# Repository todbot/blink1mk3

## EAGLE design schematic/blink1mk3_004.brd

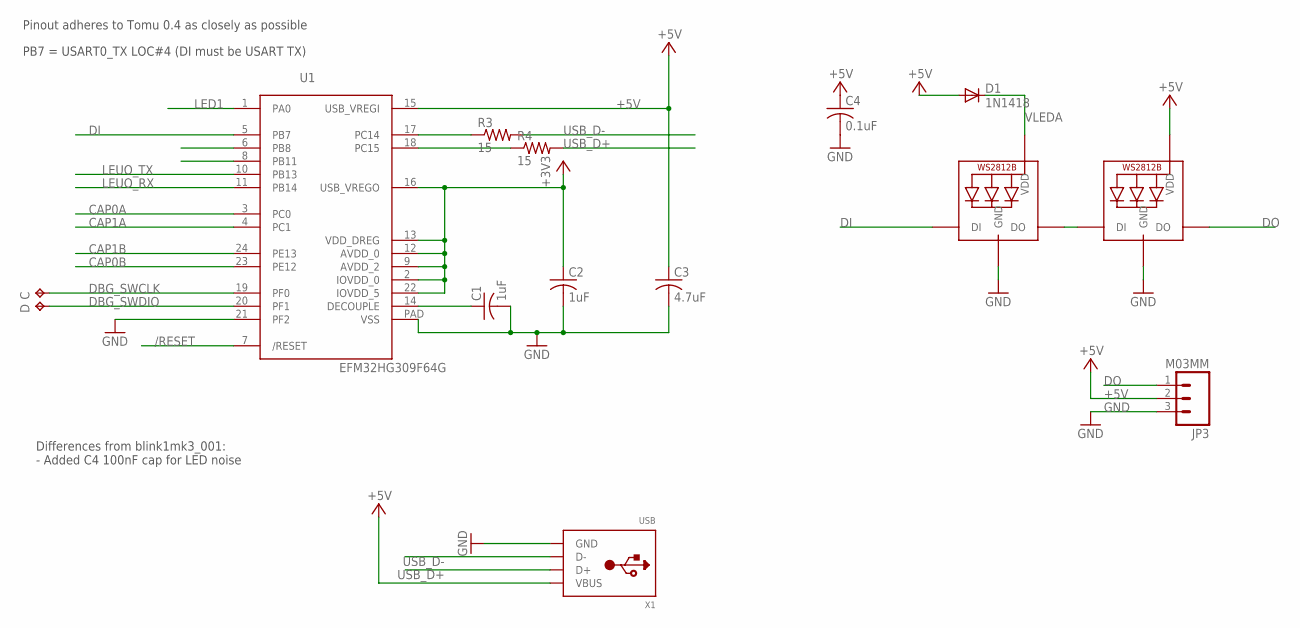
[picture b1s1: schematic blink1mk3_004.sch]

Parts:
C: TPTP10R; TP10R
C1, C2: 1uF; C0402
C3: 4.7uF; C0402
C4: 0.1uF; C0402
D: TPTP10R; TP10R
D1: 1N1418; SOD523
JP3: M03MM; 1X03-1.5MM
LED1, LED2: WS2812B3535; LED3535
R3, R4: 15; R0402
U1: EFM32HG309F64G; QFN24PAD
X1: USB; MOLEX-48037-1000

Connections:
+3V3: C2.1, U1.2 (IOVDD_0), U1.9 (AVDD_2), U1.12 (AVDD_0), U1.13 (VDD_DREG), U1.16 (USB_VREGO), U1.22 (IOVDD_5)
+5V: C3.1, C4.1, D1.A, JP3.2, LED2.2 (VDD), U1.15 (USB_VREGI), X1.1 (VBUS)
/RESET: U1.7 (/RESET)
CAP0A: U1.3 (PC0)
CAP0B: U1.23 (PE12)
CAP1A: U1.4 (PC1)
CAP1B: U1.24 (PE13)
DBG_SWCLK: C.TP, U1.19 (PF0)
DBG_SWDIO: D.TP, U1.20 (PF1)
DECOUPLE: C1.1, U1.14 (DECOUPLE)
DI: LED1.1 (DI), U1.5 (PB7)
DO: JP3.1, LED2.3 (DO)
GND: C1.2, C2.2, C3.2, C4.2, JP3.3, LED1.4 (GND), LED2.4 (GND), U1.21 (PF2), U1.PAD (VSS), X1.4 (GND)
LED1: U1.1 (PA0)
LEUO_RX: U1.11 (PB14)
LEUO_TX: U1.10 (PB13)
unnamed: LED1.3 (DO), LED2.1 (DI)
RUSB_D+: R4.1, U1.18 (PC15)
RUSB_D-: R3.1, U1.17 (PC14)
USB_D+: R4.2, X1.3 (D+)
USB_D-: R3.2, X1.2 (D-)
VLEDA: D1.C, LED1.2 (VDD)

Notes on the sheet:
PB7 = USART0_TX LOC#4 (DI must be USART TX)
Pinout adheres to Tomu 0.4 as closely as possible
Differences from blink1mk3_001: - Added C4 100nF cap for LED noise

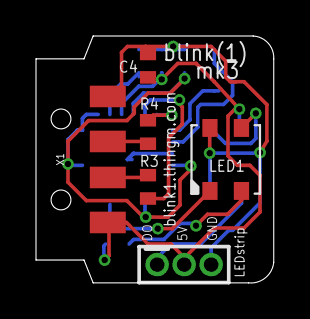
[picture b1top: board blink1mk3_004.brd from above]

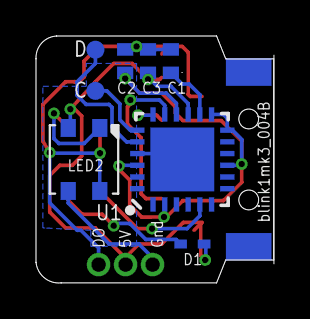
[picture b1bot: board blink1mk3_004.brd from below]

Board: 2 copper layers, 13.2 x 13.7 mm, 14 parts (8 on the bottom side), 14 nets.

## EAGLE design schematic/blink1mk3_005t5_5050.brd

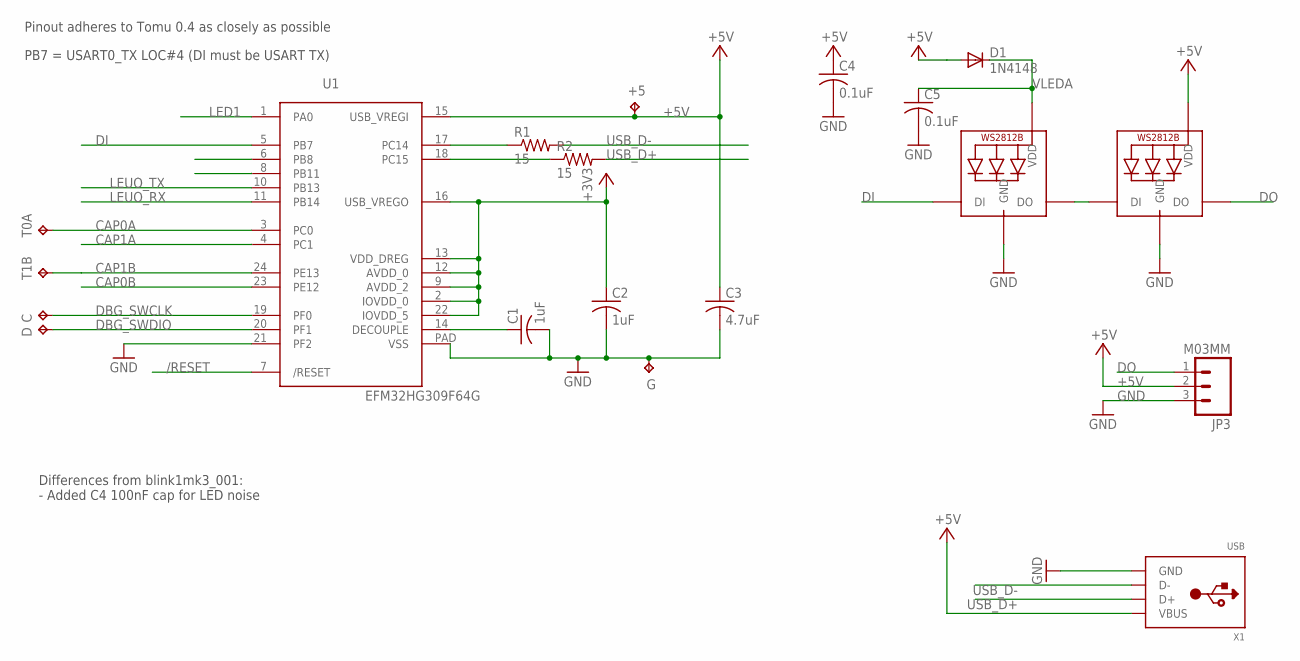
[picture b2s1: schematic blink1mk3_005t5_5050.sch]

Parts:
+5: TPTP10R; TP10R
C: TPTP10R; TP10R
C1, C2: 1uF; C0402
C3: 4.7uF; C0402
C4, C5: 0.1uF; C0402
D: TPTP10R; TP10R
D1: 1N4148; SOD523
G: TPTP10R; TP10R
JP3: M03MM; 1X03-1.5MM
LED1, LED2: SK6812MINI; WS2812B
R1, R2: 15; R0402
T0A, T1B: TPTP15R; TP15R
U1: EFM32HG309F64G; QFN24PAD
X1: USB; MOLEX-48037-1000

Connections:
+3V3: C2.1, U1.2 (IOVDD_0), U1.9 (AVDD_2), U1.12 (AVDD_0), U1.13 (VDD_DREG), U1.16 (USB_VREGO), U1.22 (IOVDD_5)
+5V: +5.TP, C3.1, C4.1, D1.A, JP3.2, LED2.1-VDD (VDD), U1.15 (USB_VREGI), X1.1 (VBUS)
/RESET: U1.7 (/RESET)
CAP0A: T0A.TP, U1.3 (PC0)
CAP0B: U1.23 (PE12)
CAP1A: U1.4 (PC1)
CAP1B: T1B.TP, U1.24 (PE13)
DBG_SWCLK: C.TP, U1.19 (PF0)
DBG_SWDIO: D.TP, U1.20 (PF1)
DECOUPLE: C1.1, U1.14 (DECOUPLE)
DI: LED1.4-DIN (DI), U1.5 (PB7)
DO: JP3.1, LED2.2-DOUT (DO)
GND: C1.2, C2.2, C3.2, C4.2, C5.2, G.TP, JP3.3, LED1.3-GND (GND), LED2.3-GND (GND), U1.21 (PF2), U1.PAD (VSS), X1.4 (GND)
LED1: U1.1 (PA0)
LEUO_RX: U1.11 (PB14)
LEUO_TX: U1.10 (PB13)
unnamed: LED1.2-DOUT (DO), LED2.4-DIN (DI)
RUSB_D+: R2.1, U1.18 (PC15)
RUSB_D-: R1.1, U1.17 (PC14)
USB_D+: R2.2, X1.3 (D+)
USB_D-: R1.2, X1.2 (D-)
VLEDA: C5.1, D1.C, LED1.1-VDD (VDD)

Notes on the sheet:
PB7 = USART0_TX LOC#4 (DI must be USART TX)
Pinout adheres to Tomu 0.4 as closely as possible
Differences from blink1mk3_001: - Added C4 100nF cap for LED noise

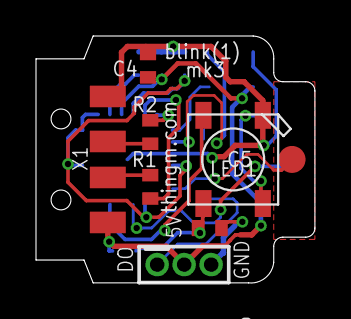
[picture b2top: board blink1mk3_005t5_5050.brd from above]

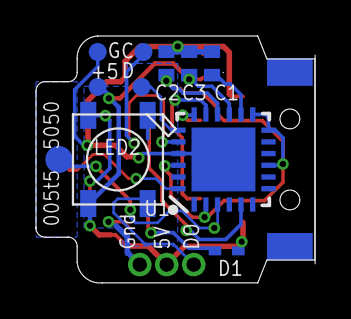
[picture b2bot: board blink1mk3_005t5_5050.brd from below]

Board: 2 copper layers, 15.5 x 13.7 mm, 19 parts (11 on the bottom side), 16 nets.
